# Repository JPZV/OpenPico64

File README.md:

# OpenPico64
Nintendo 64 flash cart using a Raspberry Pi Pico / RP2040 based on [kbeckmann](https://twitter.com/kbeckmann) [PicoCart64](https://github.com/kbeckmann/PicoCart64)

## How to build an OpenPico64

### Getting the raw PCB

- Download the `openpico64.gerber.zip` file from [Releases](https://github.com/JPZV/OpenPico64/releases/latest).

- Go to a PCB manufacturing service such as [JLCPCB](https://jlcpcb.com), [OSH Park](https://oshpark.com/), [PCBWay](https://pcbway.com) or similar.

- This takes you to the PCB configuration utility where you can upload the `.zip` from above. After uploading, you should see a rendered version of both sides of the PCB. If you want to produce a cheap cart for testing you can leave all settings as they are, except for this one:

  - ⚠️ *PCB Thickness* needs to be set to *1.2mm*, otherwise the cart won't fit in your console

⚠️ Note that this will result in a PCB with 90 degrees edges - the edge connector should be sanded down to get a nice 45 degree V shape. If this is not done, it may wear down your cart connector on the N64. The proper PCB order should be ENIG-RoHS + Gold Fingers + 45°finger chamfered, however this will result in a significant cost increase.

### Sourcing the components

In order to ensambe it you will need the following parts along with the PCBs. Here we're assuming you want to assemble 5 boards, as that is the number of PCBs you'll be getting from many PCB manufacturing services as a minimum.

⚠️ Note that this project **IS NOT** compatible with the original/oem `Raspberry Pi Pico`. **YOU HAVE** to use the [WeAct clone](https://aliexpress.com/item/1005003708090298.html) because it has more exposed pins which we need. I repeat, **DON'T** use the Raspberry Branded board (the green one with a Raspberry at the bottom), it will likely fry your N64 at best. I do recommend you to buy the 8MB version or higher, as I don't know how much will grow this project.

| Qty | Name                  | Source                                                                           | 
|-----|-----------------------|----------------------------------------------------------------------------------|
| 5   | WeAct Raspberry Pi Pico | [AliExpress](https://aliexpress.com/item/1005003708090298.html)               |       |
| 5   | BSS84 MOSFET          | [750-BSS84-HF](https://www.mouser.com/ProductDetail/750-BSS84-HF)                 |       |
| 5   | 0603 100k resistor    | [71-CRCW0603100KJNEAC](https://www.mouser.com/ProductDetail/71-CRCW0603100KJNEAC) |       |
| 5   | ATTINY85-20PU    | [556-ATTINY85-20PU](https://www.mouser.com/ProductDetail/556-ATTINY85-20PU) |       |

### Preparing the CIC (ATTiny85)

You have to flash the ATTiny85 with [UltraCIC](https://github.com/ManCloud/UltraCIC-III) before assembling everything else. You can do it with the OpenPico64 board headers to an easy installation. Then, **remember** to join the JP2 jumper!  

### Assembling the board

If your WeAct Pico didn't come with the headers ready, you'll have to solder them beforehand. Then, put the Pico on the OpenPico64 board with the USB connector facing outwards and solder the headers.

Solder the MOSFET according to the pin markings.

The resistor is optional to solder, but was placed there for good measure. (There is a resistor on the Pico, so it is not strictly needed.)

### Flashing/Updating the firmware

Go to the [Releases](https://github.com/JPZV/OpenPico64/releases/latest) and download the latest .UF2 file. **Remove the OpenPico64 from your N64**, then press and hold the **BOOTSEL** button while connecting the Pico to your computer. Open your file explorer (Explorer on Windows, Fiddle on Mac, and file manager in Linux), navigate to the new Flash memory, copy and paste the .UF2, and wait until it closes.

⚠️ **DON'T** use your OpenPico64 in your N64 while it's connected to your PC or anything. The N64 works with 3.3V and your computer with 5V, so likely it'll fry your N64.

## License

The PCB is licensed under the following license: "CERN Open Hardware Licence Version 2 - Permissive" aka "CERN-OHL-P".

The software is licensed under BSD-2-Clause unless otherwise specified.

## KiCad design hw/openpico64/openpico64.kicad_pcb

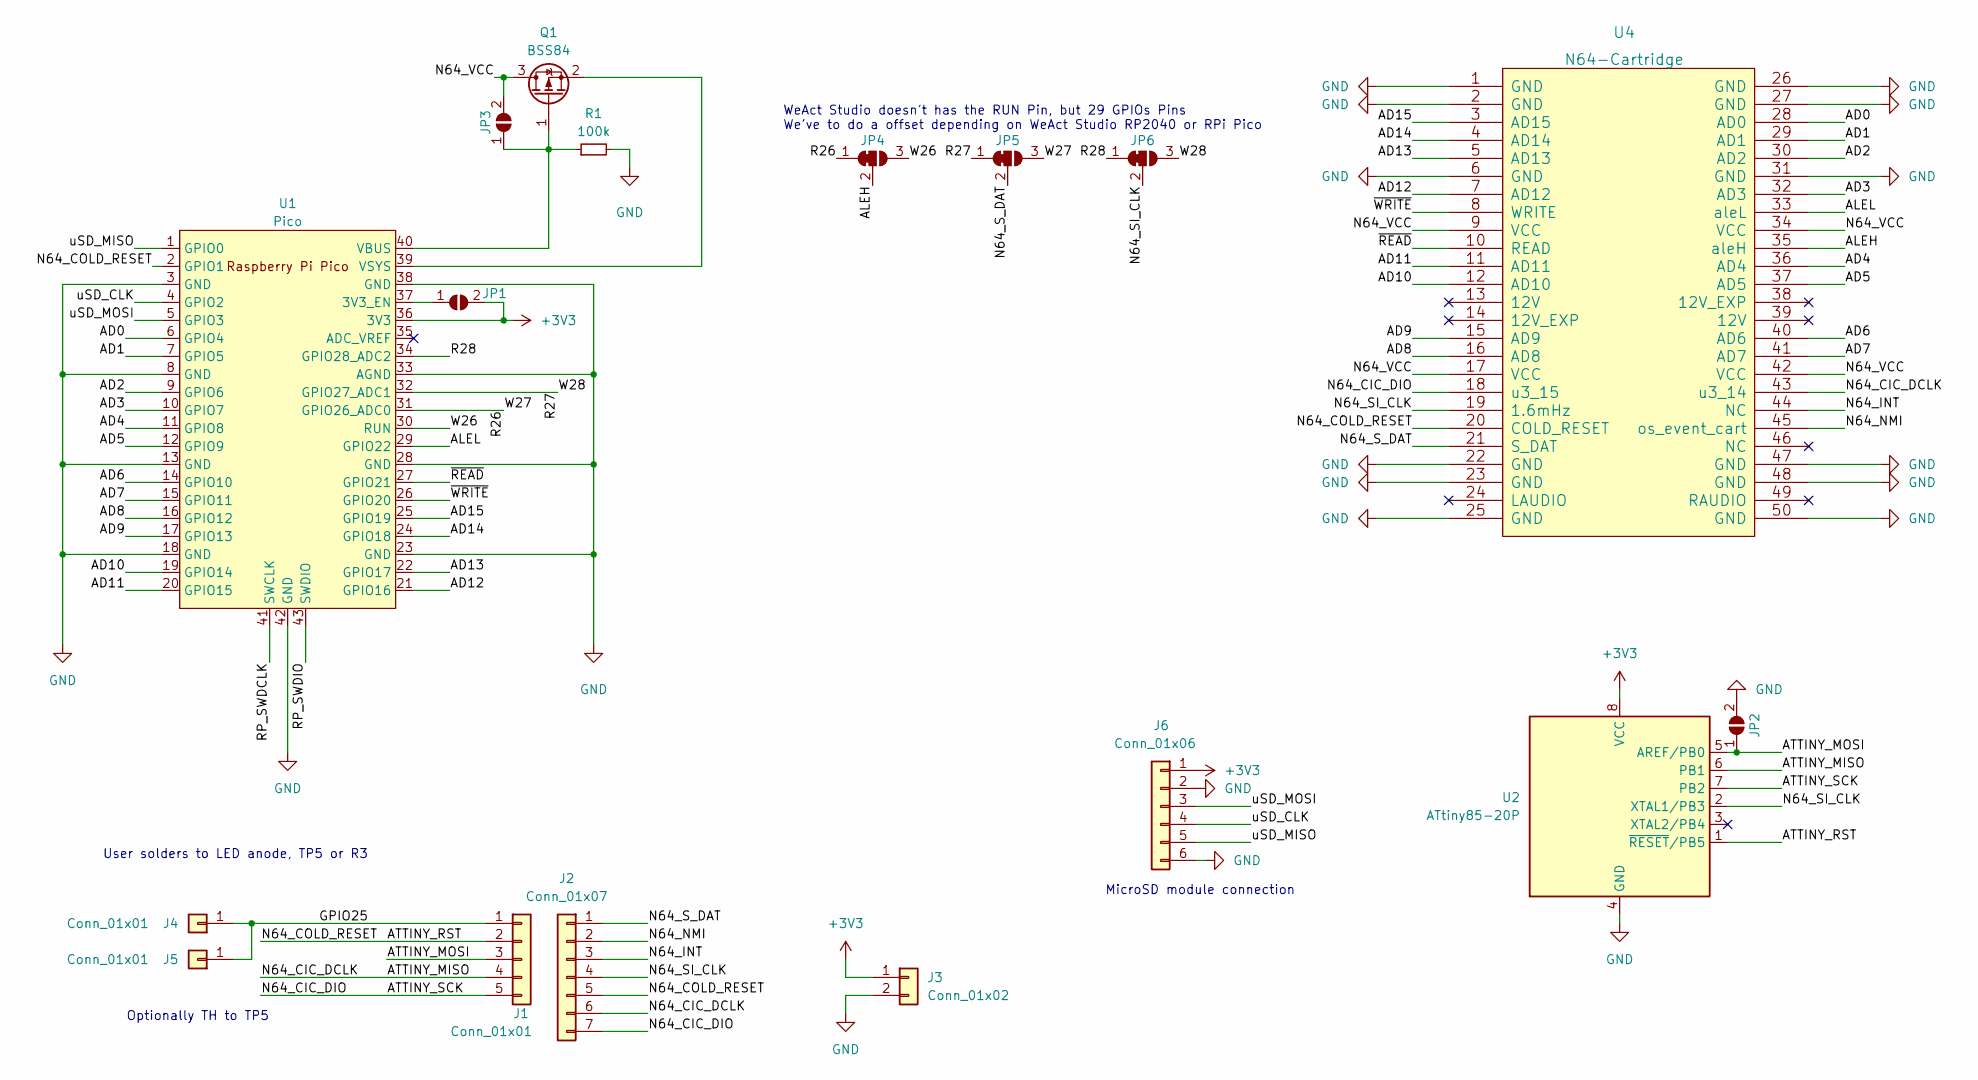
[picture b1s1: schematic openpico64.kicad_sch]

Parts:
J1: Conn_01x01; PinHeader_1x05_P2.54mm_Vertical
J2: Conn_01x07; PinHeader_1x07_P2.54mm_Vertical
J3: Conn_01x02; PinHeader_1x08_P2.54mm_Vertical
J4, J5: Conn_01x01; PinHeader_1x01_P2.54mm_Vertical
J6: Conn_01x06; PinHeader_1x06_P2.54mm_Vertical
JP1, JP2, JP3: SolderJumper_2_Open; SolderJumper-2_P1.3mm_Open_RoundedPad1.0x1.5mm
JP4, JP5, JP6: SolderJumper_3_Bridged12; SolderJumper-3_P1.3mm_Bridged12_RoundedPad1.0x1.5mm_NumberL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
Q1: BSS84; SOT-23
R1: 100k; R_0603_1608Metric_Pad0.98x0.95mm_HandSolder
U1: Pico; RPi_Pico_SMD_TH
U2: ATtiny85-20P; DIP-8_W7.62mm
U4: N64-Cartridge; N64-Connector

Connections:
+3V3: J3.1, J6.1, JP1.2 (B), U1.36 (3V3), U2.8 (VCC)
/AD0: U1.6 (GPIO4), U4.28 (AD0)
/AD1: U1.7 (GPIO5), U4.29 (AD1)
/AD2: U1.9 (GPIO6), U4.30 (AD2)
/AD3: U1.10 (GPIO7), U4.32 (AD3)
/AD4: U1.11 (GPIO8), U4.36 (AD4)
/AD5: U1.12 (GPIO9), U4.37 (AD5)
/AD6: U1.14 (GPIO10), U4.40 (AD6)
/AD7: U1.15 (GPIO11), U4.41 (AD7)
/AD8: U1.16 (GPIO12), U4.16 (AD8)
/AD9: U1.17 (GPIO13), U4.15 (AD9)
/AD10: U1.19 (GPIO14), U4.12 (AD10)
/AD11: U1.20 (GPIO15), U4.11 (AD11)
/AD12: U1.21 (GPIO16), U4.7 (AD12)
/AD13: U1.22 (GPIO17), U4.5 (AD13)
/AD14: U1.24 (GPIO18), U4.4 (AD14)
/AD15: U1.25 (GPIO19), U4.3 (AD15)
/ALEH: JP4.2 (C), U4.35 (aleH)
/ALEL: U1.29 (GPIO22), U4.33 (aleL)
/ATTINY_MISO: J1.4, J2.6, U2.6 (PB1), U4.43 (u3_14)
/ATTINY_MOSI: J1.3, JP2.1 (A), U2.5 (AREF/PB0)
/ATTINY_RST: J1.2, J2.5, U1.2 (GPIO1), U2.1 (~RESET/PB5), U4.20 (COLD_RESET)
/ATTINY_SCK: J1.5, J2.7, U2.7 (PB2), U4.18 (u3_15)
/GPIO25: J1.1, J4.1, J5.1
/N64_INT: J2.3, U4.44 (NC)
/N64_NMI: J2.2, U4.45 (os_event_cart)
/N64_SI_CLK: J2.4, JP6.2 (C), U2.2 (XTAL1/PB3), U4.19 (1.6mHz)
/N64_S_DAT: J2.1, JP5.2 (C), U4.21 (S_DAT)
/N64_VCC: JP3.2 (B), Q1.3 (D), U4.9 (VCC), U4.17 (VCC), U4.34 (VCC), U4.42 (VCC)
/R26: JP4.1 (A), JP5.3 (B), U1.31 (GPIO26_ADC0)
/R27: JP5.1 (A), JP6.3 (B), U1.32 (GPIO27_ADC1)
/R28: JP6.1 (A), U1.34 (GPIO28_ADC2)
/RP_SWDCLK: U1.41 (SWCLK)
/RP_SWDIO: U1.43 (SWDIO)
/W26: JP4.3 (B), U1.30 (RUN)
/uSD_CLK: J6.4, U1.4 (GPIO2)
/uSD_MISO: J6.5, U1.1 (GPIO0)
/uSD_MOSI: J6.3, U1.5 (GPIO3)
/~READ: U1.27 (GPIO21), U4.10 (READ)
/~WRITE: U1.26 (GPIO20), U4.8 (WRITE)
GND: J3.2, J6.2, J6.6, JP2.2 (B), R1.2, U1.3 (GND), U1.8 (GND), U1.13 (GND), U1.18 (GND), U1.23 (GND), U1.28 (GND), U1.33 (AGND), U1.38 (GND), U1.42 (GND), U2.4 (GND), U4.1 (GND), U4.2 (GND), U4.6 (GND), U4.22 (GND), U4.23 (GND), U4.25 (GND), U4.26 (GND), U4.27 (GND), U4.31 (GND), U4.47 (GND), U4.48 (GND), U4.50 (GND)
unnamed: JP1.1 (A), U1.37 (3V3_EN)
unnamed: JP3.1 (A), Q1.1 (G), R1.1, U1.40 (VBUS)
unnamed: Q1.2 (S), U1.39 (VSYS)

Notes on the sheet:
WeAct Studio doesn't has the RUN Pin, but 29 GPIOs Pins We've to do a offset depending on WeAct Studio RP2040 or RPi Pico
User solders to LED anode, TP5 or R3
Optionally TH to TP5
MicroSD module connection

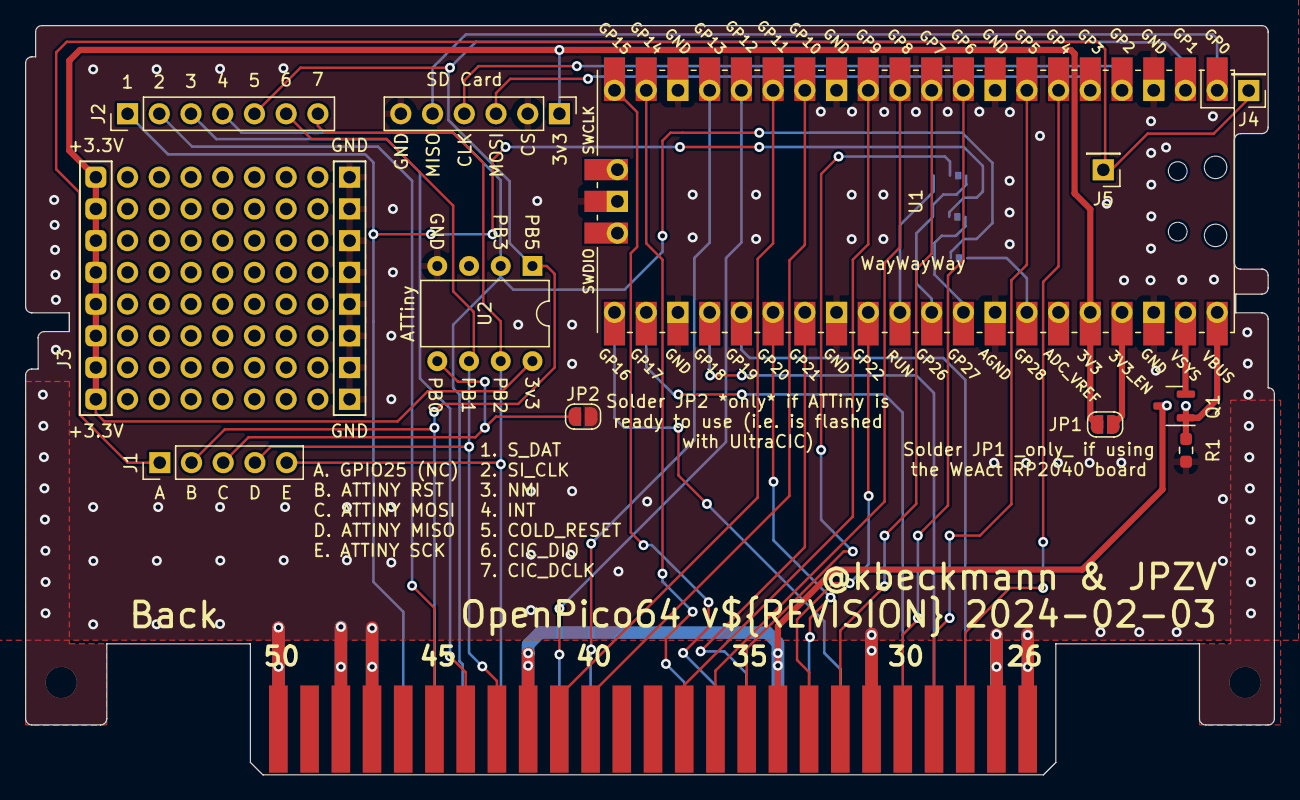
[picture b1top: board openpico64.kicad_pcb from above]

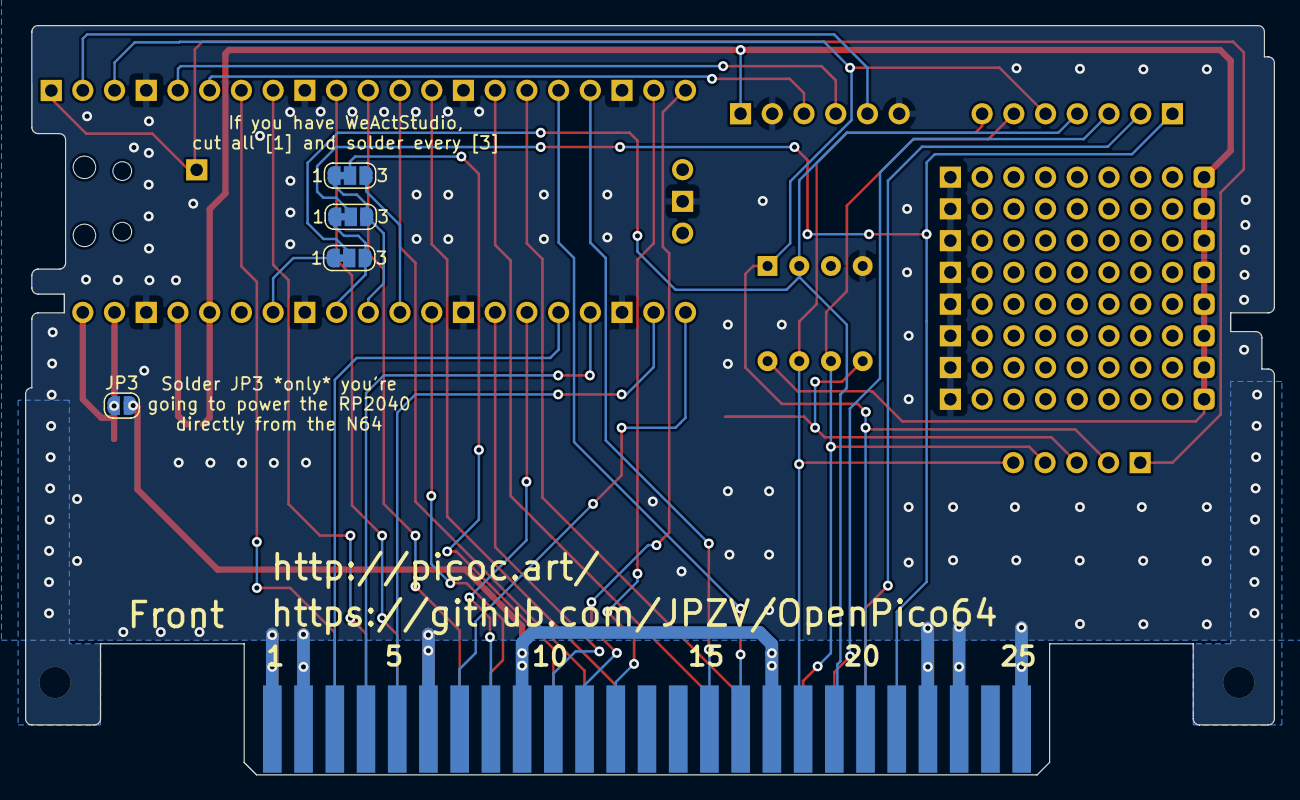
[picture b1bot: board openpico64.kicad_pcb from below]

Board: 2 copper layers, 100.0 x 60.0 mm, 17 parts (5 on the bottom side), 42 nets.

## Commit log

2026-06-16 Renamed PicoCart64 to OpenPico64
2026-06-16 Converted libdragon into submodule
2026-06-16 Removed gerber files
2026-06-16 Moved CIC to separated IC
    this helps us to allocate more pins
2026-06-16 [WIP] Implemented loading games from SD
2026-06-16 Updating the README
2026-06-16 Fixed submodule not present in Git
2026-06-16 Create c_cpp_properties.json
    This fixes the intellisense
2026-06-19 Fixed TestRom makefile to make it compatible with latest LibDragon
